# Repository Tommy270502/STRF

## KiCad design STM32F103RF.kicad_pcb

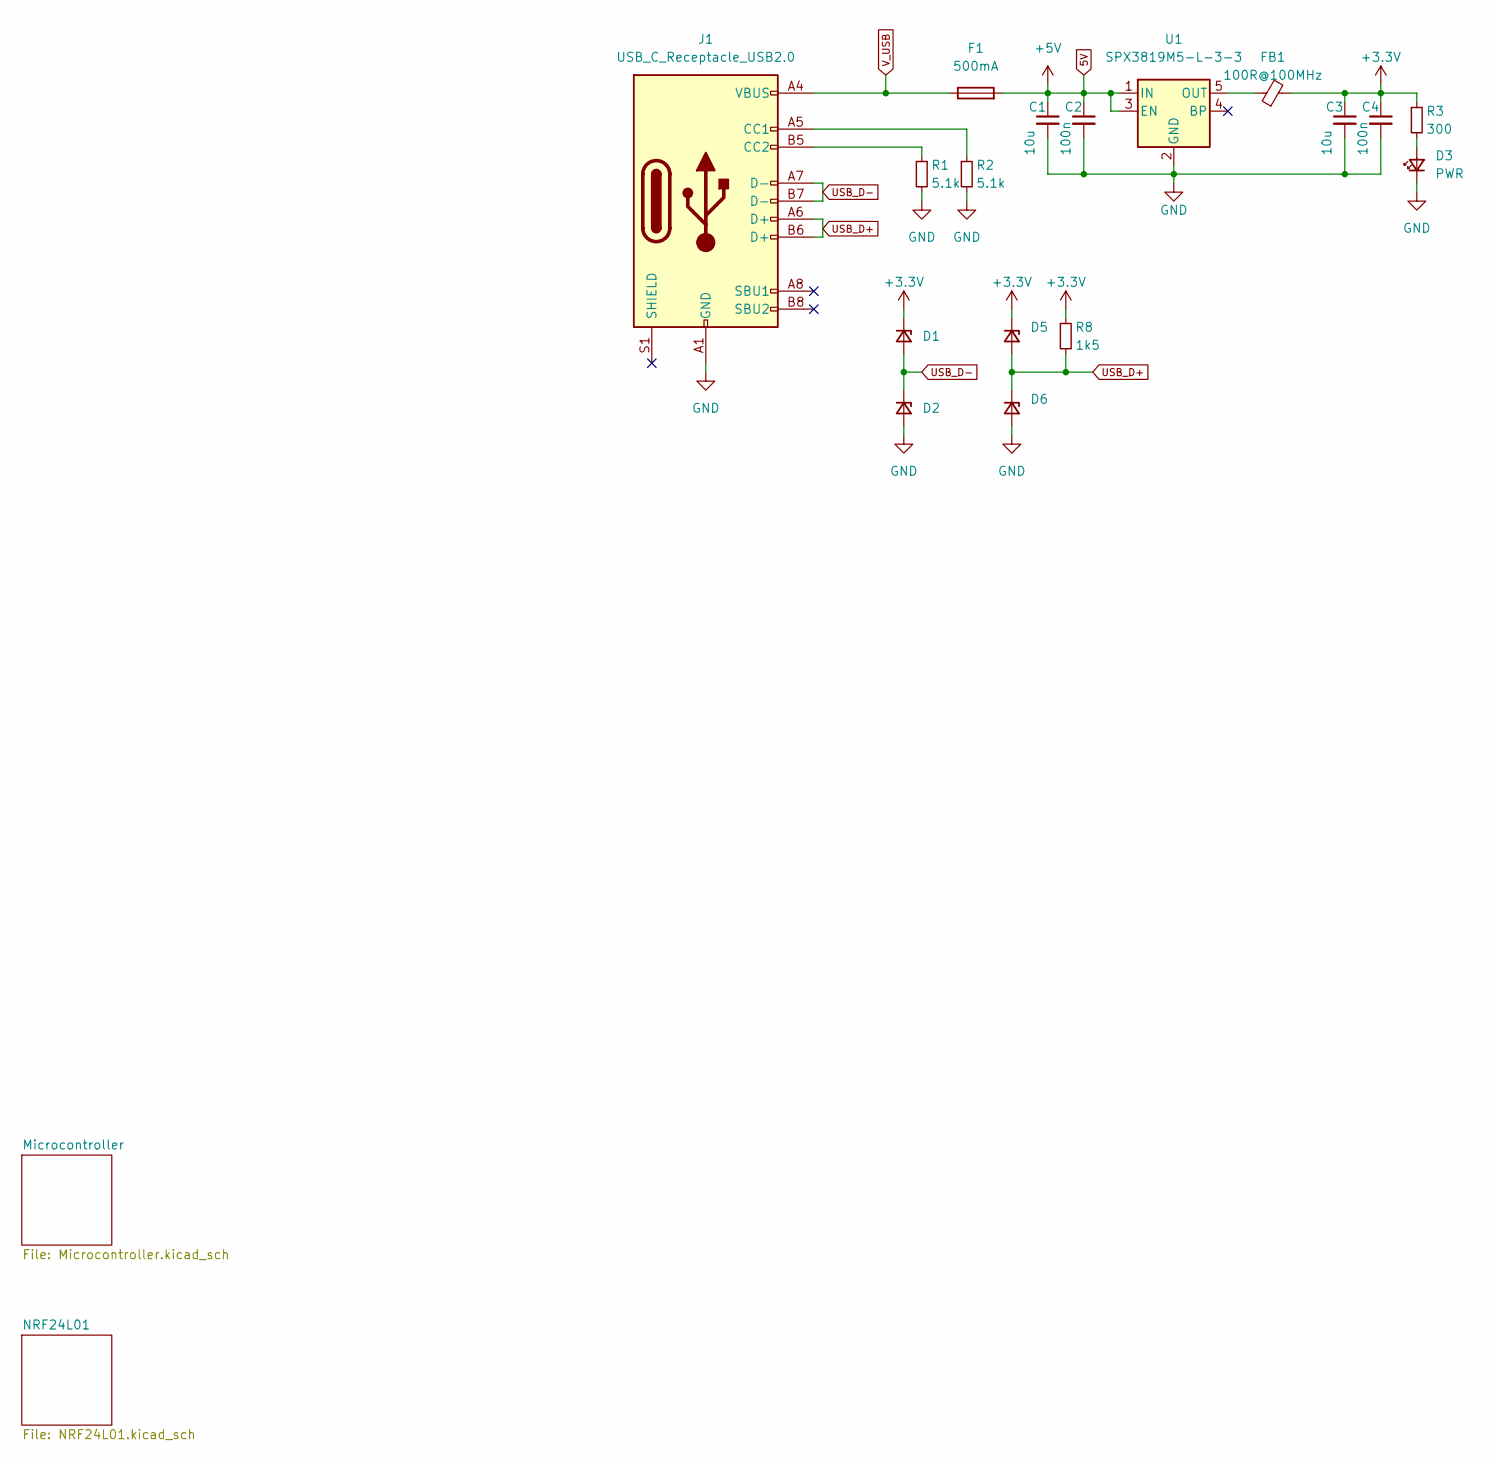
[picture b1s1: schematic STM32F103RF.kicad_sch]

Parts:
C1, C3: 10u; C_0603_1608Metric_Pad1.08x0.95mm_HandSolder
C2, C4: 100n; C_0603_1608Metric_Pad1.08x0.95mm_HandSolder
D1, D2, D5, D6: D_Zener_Small; D_SOD-323_HandSoldering
D3: PWR; LED_0603_1608Metric_Pad1.05x0.95mm_HandSolder
F1: 500mA; Fuse_0603_1608Metric_Pad1.05x0.95mm_HandSolder
FB1: 100R@100MHz; L_0603_1608Metric_Pad1.05x0.95mm_HandSolder
J1: USB_C_Receptacle_USB2.0; USB_C_Receptacle_HRO_TYPE-C-31-M-12
R1, R2: 5.1k; R_0603_1608Metric_Pad0.98x0.95mm_HandSolder
R3: 300; R_0603_1608Metric_Pad0.98x0.95mm_HandSolder
R8: 1k5; R_0603_1608Metric_Pad0.98x0.95mm_HandSolder
U1: SPX3819M5-L-3-3; SOT-23-5

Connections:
3.3V: C3.1, C4.1, D1.1 (K), D5.1 (K), FB1.2, R3.1, R8.1; also elsewhere on the board
5V: C1.1, C2.1, F1.2, U1.1 (IN), U1.3 (EN)
GND: C1.2, C2.2, C3.2, C4.2, D2.2 (A), D3.1 (K), D6.2 (A), J1.A1 (GND), J1.A12 (GND), J1.B1 (GND), J1.B12 (GND), R1.2, R2.2, U1.2 (GND); also elsewhere on the board
unnamed: D3.2 (A), R3.2
unnamed: FB1.1, U1.5 (OUT)
unnamed: J1.A5 (CC1), R2.1
unnamed: J1.B5 (CC2), R1.1
USBCON_D-: D1.2 (A), D2.1 (K), J1.A7 (D-), J1.B7 (D-); also elsewhere on the board
V_USB: F1.1, J1.A4 (VBUS), J1.A9 (VBUS), J1.B4 (VBUS), J1.B9 (VBUS)

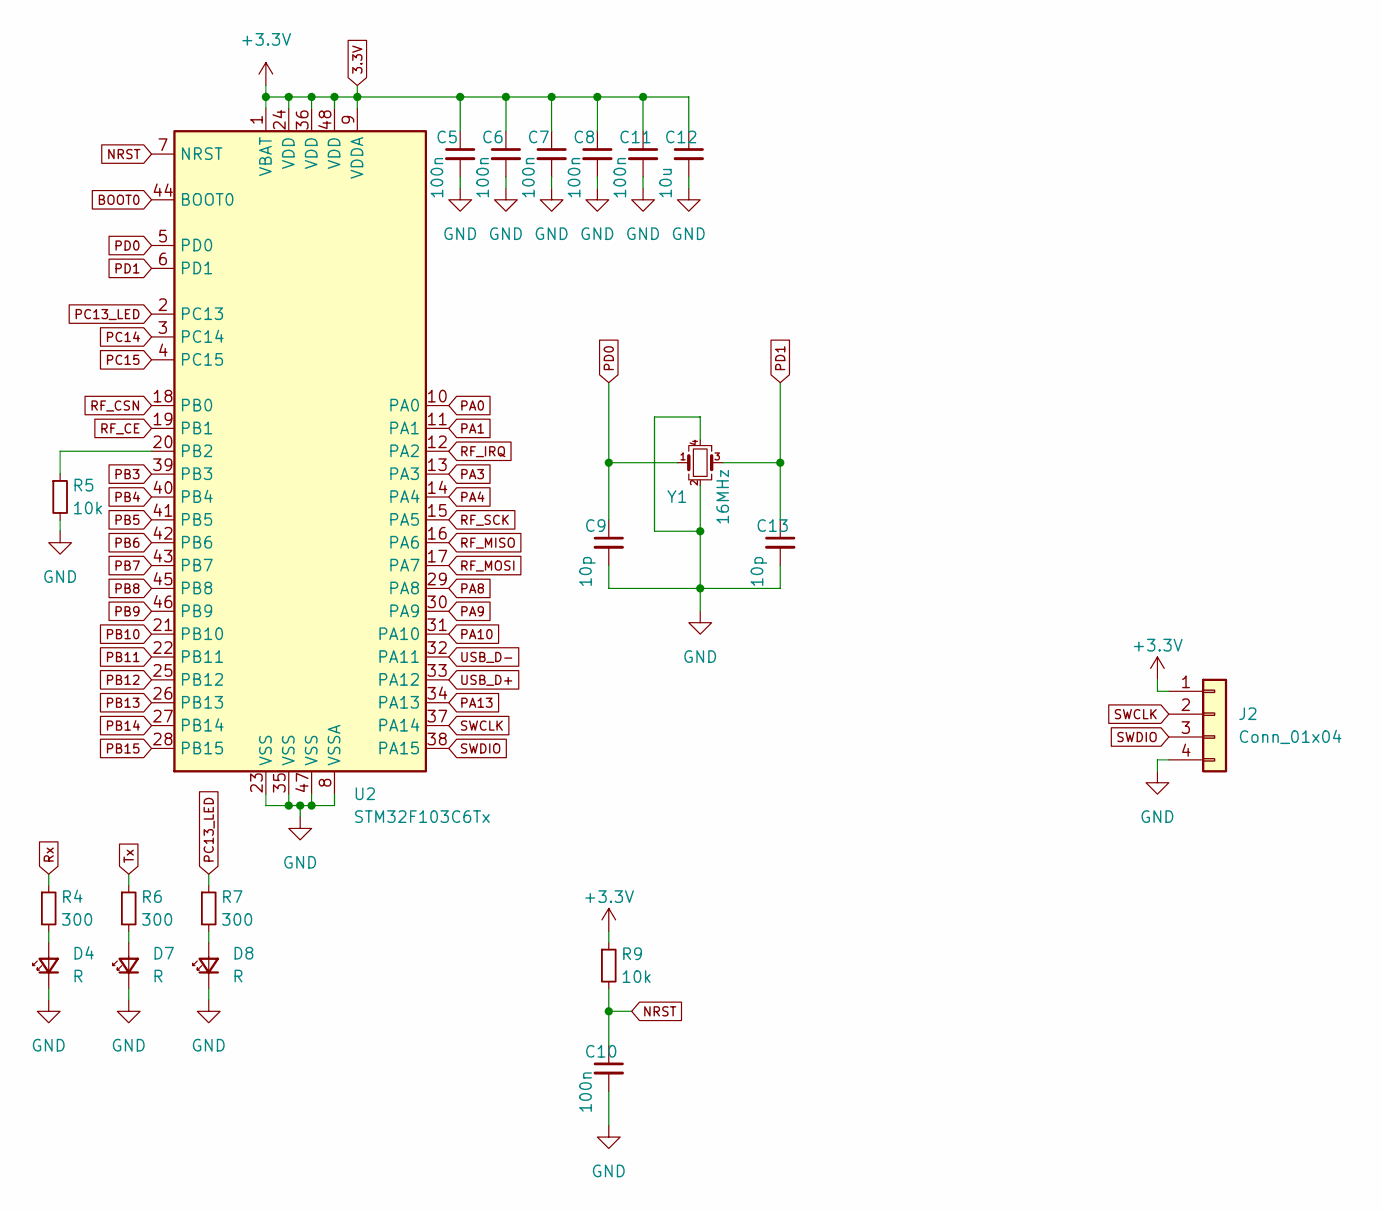
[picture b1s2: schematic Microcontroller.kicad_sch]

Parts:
C5, C6, C7, C8, C10, C11: 100n; C_0603_1608Metric_Pad1.08x0.95mm_HandSolder
C9, C13: 10p; C_0603_1608Metric_Pad1.08x0.95mm_HandSolder
C12: 10u; C_0603_1608Metric_Pad1.08x0.95mm_HandSolder
D4, D7, D8: R; LED_0603_1608Metric_Pad1.05x0.95mm_HandSolder
J2: Conn_01x04; PinHeader_1x04_P2.54mm_Vertical
R4, R6, R7: 300; R_0603_1608Metric_Pad0.98x0.95mm_HandSolder
R5, R9: 10k; R_0603_1608Metric_Pad0.98x0.95mm_HandSolder
U2: STM32F103C6Tx; LQFP-48_7x7mm_P0.5mm
Y1: 16MHz; Crystal_SMD_2520-4Pin_2.5x2.0mm

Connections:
3.3V: C5.1, C6.1, C7.1, C8.1, C11.1, C12.1, J2.1, R9.1, U2.1 (VBAT), U2.9 (VDDA), U2.24 (VDD), U2.36 (VDD), U2.48 (VDD); also elsewhere on the board
BOOT0: U2.44 (BOOT0)
GND: C5.2, C6.2, C7.2, C8.2, C9.2, C10.2, C11.2, C12.2, C13.2, D4.1 (K), D7.1 (K), D8.1 (K), J2.4, R5.2, U2.8 (VSSA), U2.23 (VSS), U2.35 (VSS), U2.47 (VSS), Y1.2, Y1.4; also elsewhere on the board
NRST: C10.1, R9.2, U2.7 (NRST)
unnamed: D4.2 (A), R4.2
unnamed: D7.2 (A), R6.2
unnamed: D8.2 (A), R7.2
unnamed: R5.1, U2.20 (PB2)
PA0: U2.10 (PA0)
PA1: U2.11 (PA1)
PA3: U2.13 (PA3)
PA4: U2.14 (PA4)
PA8: U2.29 (PA8)
PA9: U2.30 (PA9)
PA10: U2.31 (PA10)
PA13: U2.34 (PA13)
PB3: U2.39 (PB3)
PB4: U2.40 (PB4)
PB5: U2.41 (PB5)
PB6: U2.42 (PB6)
PB7: U2.43 (PB7)
PB8: U2.45 (PB8)
PB9: U2.46 (PB9)
PB10: U2.21 (PB10)
PB11: U2.22 (PB11)
PB12: U2.25 (PB12)
PB13: U2.26 (PB13)
PB14: U2.27 (PB14)
PB15: U2.28 (PB15)
PC13_LED: R7.1, U2.2 (PC13)
PC14: U2.3 (PC14)
PC15: U2.4 (PC15)
PD0: C9.1, U2.5 (PD0), Y1.1
PD1: C13.1, U2.6 (PD1), Y1.3
RF_CE: U2.19 (PB1); also elsewhere on the board
RF_CSN: U2.18 (PB0); also elsewhere on the board
RF_IRQ: U2.12 (PA2); also elsewhere on the board
RF_MISO: U2.16 (PA6); also elsewhere on the board
RF_MOSI: U2.17 (PA7); also elsewhere on the board
RF_SCK: U2.15 (PA5); also elsewhere on the board
Rx: R4.1
SWCLK: J2.2, U2.37 (PA14)
SWDIO: J2.3, U2.38 (PA15)
Tx: R6.1
USB_D-: U2.32 (PA11); also elsewhere on the board

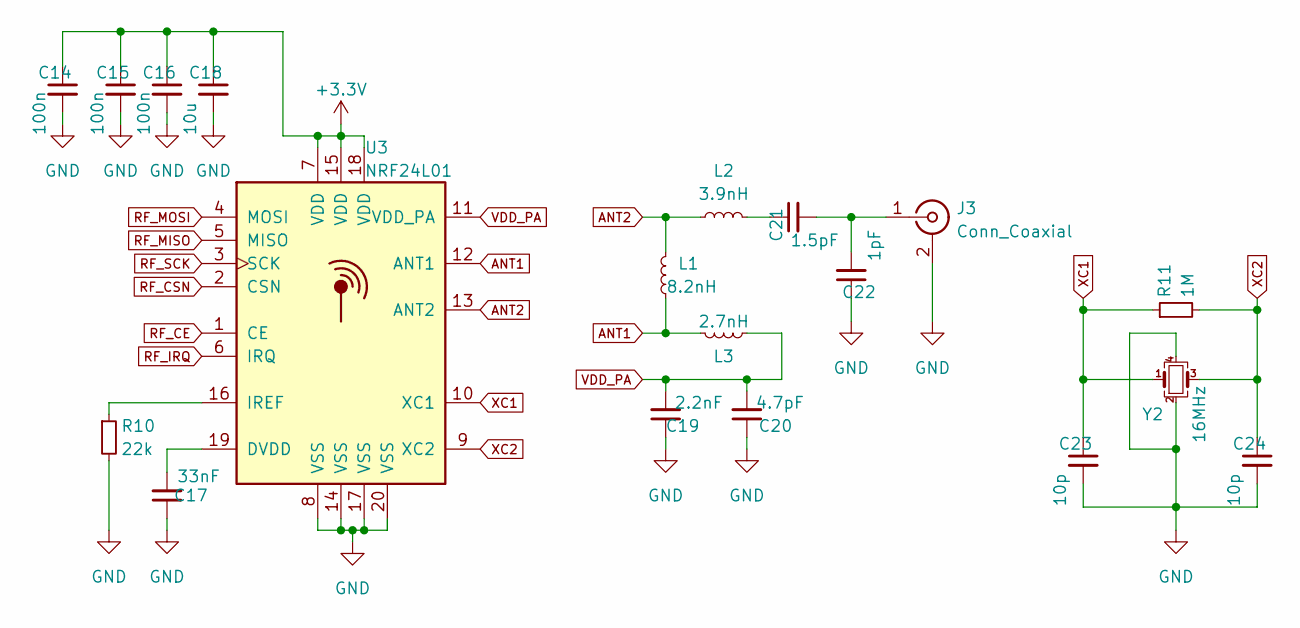
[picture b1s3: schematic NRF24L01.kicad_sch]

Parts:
C14, C15, C16: 100n; C_0603_1608Metric_Pad1.08x0.95mm_HandSolder
C17: 33nF; C_0603_1608Metric_Pad1.08x0.95mm_HandSolder
C18: 10u; C_0603_1608Metric_Pad1.08x0.95mm_HandSolder
C19: 2.2nF; C_0603_1608Metric_Pad1.08x0.95mm_HandSolder
C20: 4.7pF; C_0603_1608Metric_Pad1.08x0.95mm_HandSolder
C21: 1.5pF; C_0603_1608Metric_Pad1.08x0.95mm_HandSolder
C22: 1pF; C_0603_1608Metric_Pad1.08x0.95mm_HandSolder
C23, C24: 10p; C_0603_1608Metric_Pad1.08x0.95mm_HandSolder
J3: Conn_Coaxial; SMA_Samtec_SMA-J-P-X-ST-EM1_EdgeMount
L1: 8.2nH; L_0603_1608Metric_Pad1.05x0.95mm_HandSolder
L2: 3.9nH; L_0603_1608Metric_Pad1.05x0.95mm_HandSolder
L3: 2.7nH; L_0603_1608Metric_Pad1.05x0.95mm_HandSolder
R10: 22k; R_0603_1608Metric_Pad0.98x0.95mm_HandSolder
R11: 1M; R_0603_1608Metric_Pad0.98x0.95mm_HandSolder
U3: NRF24L01; QFN-20-1EP_4x4mm_P0.5mm_EP2.5x2.5mm
Y2: 16MHz; Crystal_SMD_2520-4Pin_2.5x2.0mm

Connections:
3.3V: C14.1, C15.1, C16.1, C18.1, U3.7 (VDD), U3.15 (VDD), U3.18 (VDD); also elsewhere on the board
ANT1: L1.1, L3.2, U3.12 (ANT1)
ANT2: L1.2, L2.1, U3.13 (ANT2)
GND: C14.2, C15.2, C16.2, C17.1, C18.2, C19.1, C20.1, C22.1, C23.2, C24.2, J3.2 (Ext), R10.2, U3.8 (VSS), U3.14 (VSS), U3.17 (VSS), U3.20 (VSS), Y2.2, Y2.4; also elsewhere on the board
unnamed: C17.2, U3.19 (DVDD)
unnamed: C21.1, L2.2
unnamed: C21.2, C22.2, J3.1 (In)
unnamed: R10.1, U3.16 (IREF)
RF_CE: U3.1 (CE); also elsewhere on the board
RF_CSN: U3.2 (CSN); also elsewhere on the board
RF_IRQ: U3.6 (IRQ); also elsewhere on the board
RF_MISO: U3.5 (MISO); also elsewhere on the board
RF_MOSI: U3.4 (MOSI); also elsewhere on the board
RF_SCK: U3.3 (SCK); also elsewhere on the board
VDD_PA: C19.2, C20.2, L3.1, U3.11 (VDD_PA)
XC1: C23.1, R11.1, U3.10 (XC1), Y2.1
XC2: C24.1, R11.2, U3.9 (XC2), Y2.3

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
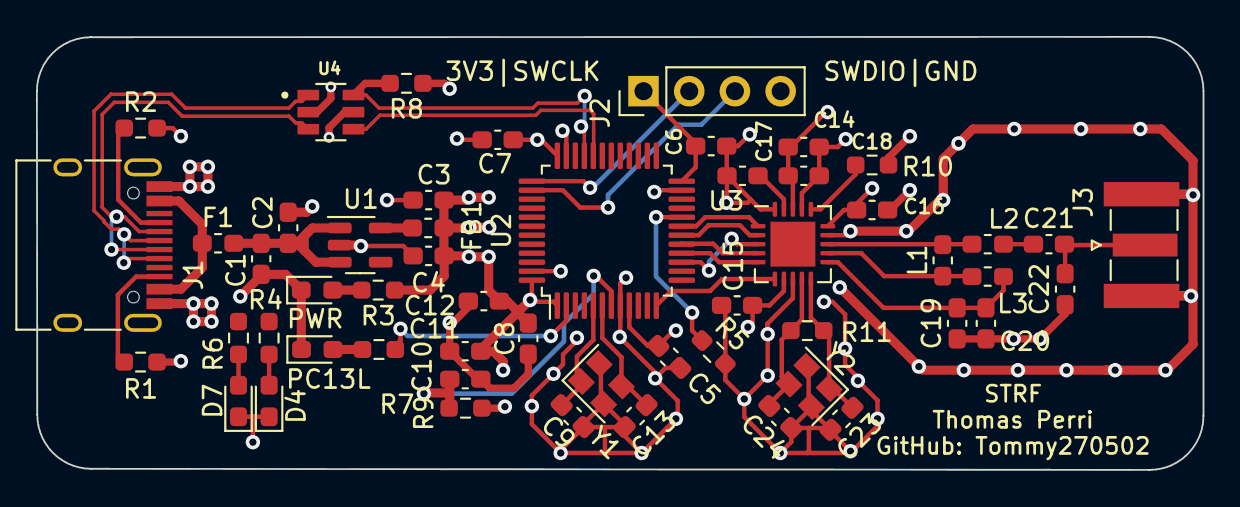
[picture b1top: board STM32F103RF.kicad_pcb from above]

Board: 4 copper layers, 64.8 x 24.1 mm, 53 parts (0 on the bottom side), 37 nets.

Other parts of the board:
U4: USBLC6-2SC6; SOT95P280X145-6N

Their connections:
3.3V: U4.5; also elsewhere on the board
GND: U4.2; also elsewhere on the board
USBCON_D-: U4.3; also elsewhere on the board
USB_D-: U4.4; also elsewhere on the board

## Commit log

2022-11-26 First commit!
2022-11-26 Added usbc
2022-11-27 placing usb components
2022-11-27 4-layer stackup & some rough component placement
2022-11-27 sum layouting
2022-11-27 fixing repo hopefully
2022-11-27 minor changes
2022-11-27 added usbc and crystal 3d models
2022-11-27 removed sma connector -> wrong footprint
2022-11-27 fixed footprints and added 3d models
2022-11-27 added pictures and BOM
2022-11-28 shortened pcb by moving sma connector closer to the center
2022-11-28 poured all copper planes
2022-11-28 generated gerber files to test if production ready
2022-11-28 zipped
2022-11-28 fixed unconnected bottom side GND of connector and other missing connections
2022-11-28 removed STRFV1 gerber
2022-11-28 generated STRFV2 gerber
2022-11-28 still fixing some polygons and shifting vias
2022-12-08 redid some power vias
2022-12-12 updated pictures
2022-12-12 added proper ESD Protection for USB
2022-12-12 added 3d model
2022-12-12 updated usb layout and pictures
